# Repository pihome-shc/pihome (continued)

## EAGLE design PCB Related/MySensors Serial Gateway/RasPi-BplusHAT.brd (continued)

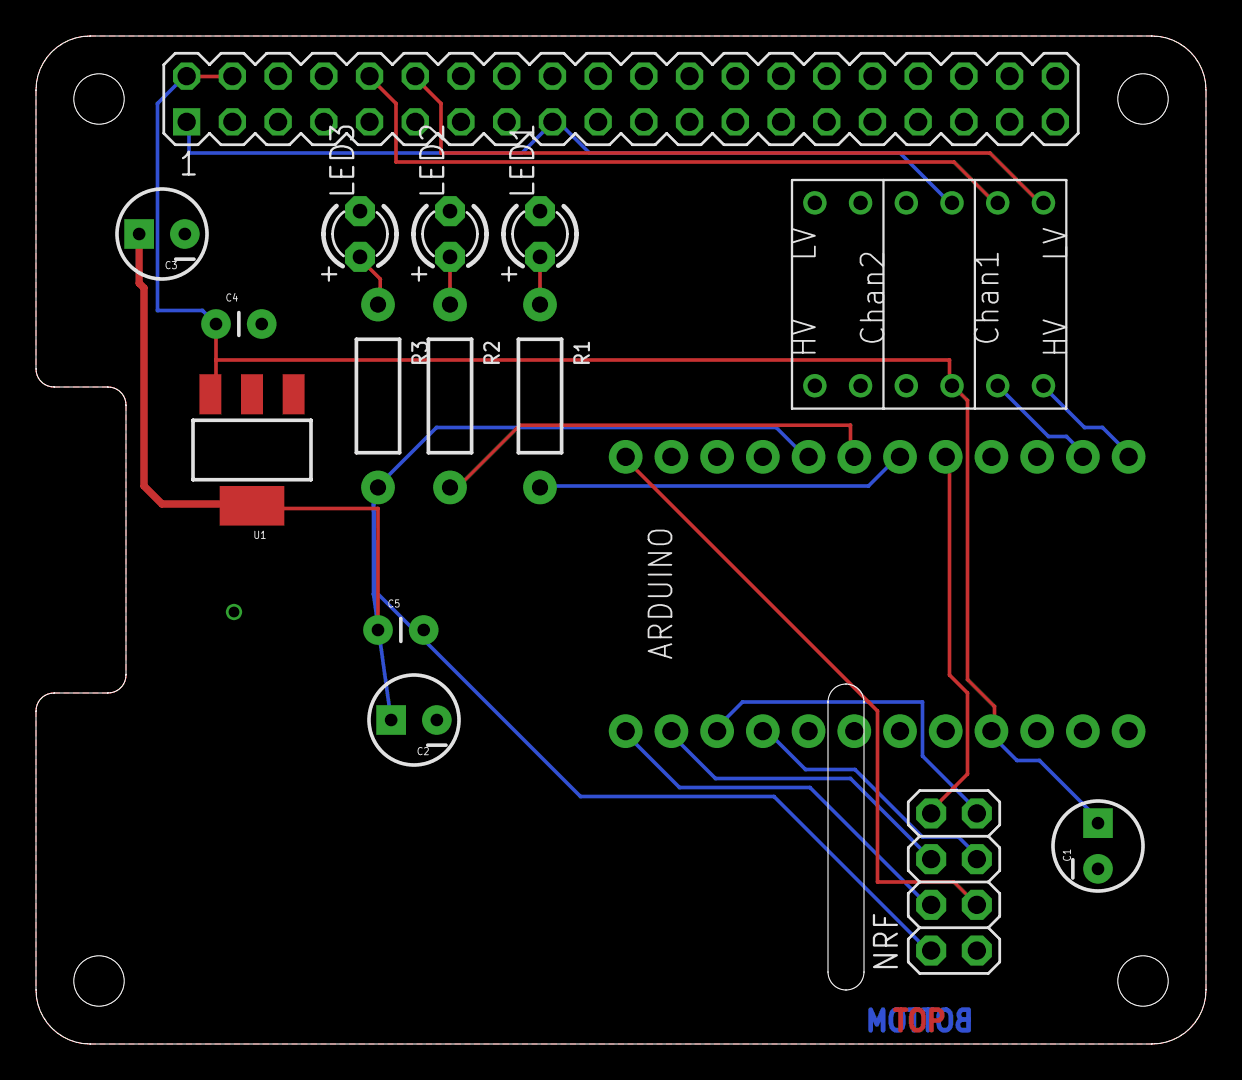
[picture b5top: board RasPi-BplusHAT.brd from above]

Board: 2 copper layers, 65.0 x 56.0 mm, 16 parts (0 on the bottom side), 20 nets.

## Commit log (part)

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2020-06-24 Update chart_load.php
    #291 changed the query from year to week and day
2020-06-25 chart load time
    reduce loading time for charts, battery voltage graph is removed.
2020-06-25 buttons for chart
    adding bigger buttons same as settings.
2020-06-28 Typo
2020-06-29 Update gpio_ds18b20.py
    gpio connected temperature senosrs,
    Charts #291
2020-06-29 Update mqtt.py
    MQTT client update: compatible with python version 3
2020-06-30 Update gateway.py
    root@pihome:~# python /var/www/cron/gateway.py
    File "/var/www/cron/gateway.py", line 223
    if (node_id != 0 and child_sensor_id != 255 and message_type == 1 and sub_type == 24):
    ^
    TabError: inconsistent use of tabs and spaces in indentation
2020-07-02 Update zone.php
    half fix for: Zone - Add - message_out not updating/populating
2020-07-09 Update db_config.ini
    chnaged the build number.
2020-07-11 MySensors Nodes without ID
    MySensors Nodes without ID #321
2020-07-13 small changes to update setup db script
    small changes to update setup db script
2020-07-14 Update gpio_ds18b20.py
    ds18B20 Wired DS18B20 Sensors and Graphs
2020-07-15 zone_type
    sync and purge column added for zone_type
    #24
2020-07-15 zone_table
    zone_table where purge is 0
    #24
2020-07-15 zone_type for db update and db setup
    #24
2020-07-15 fix for scheduling bug #331
    Bug - Scheduling #331
2020-07-17 Update zone.php
    on changing or creating zone sync value set to 0 to sync with Piconnect
    #24
2020-07-19 Update pihome_mysql_database.sql
    #24 making zone_current_state table compatible with PiConnect
2020-07-19 Update pihome_mysql_database.sql
    #24
2020-07-19 Making code compatible with PiConnect
    Making code compatible with PiConnect
    #24
2020-07-19 Update db_config.ini
    #24
2020-07-19 Update update_db.php
    #24
2020-07-19 Update boiler.php
    #24
2020-08-03 Update boiler.php
    Small fix to call home
2020-08-05 version 1.76
    version 1.76
2020-08-05 schedule name
    Schedule name on home screen moved next to zone temperature
2020-08-08 Update db.php
    sync status set to chanve for add_on #247
2020-08-18 zone editing and battery level duplicate div removed
    Zone Editing fixed updating zone_sensors table
    batteryusage: duplicate div for battery level removed.
2020-08-25 Update en.php
    Thank to Kevin for fixing typing errors.
2020-08-28 Update en.php
    improved language, thanks for Kevin for working on this.
2020-08-28 German translation
    German translation #383
2020-08-28 German translation
    #383 German translation
2020-09-09 Update boiler.php
    #391
2020-09-18 Initialization of $zone_controllers array for every zone
    Zone controllers array was not initialized for every zone, as result if zone had more than one controller and following zones executed in boiler script had less controllers, controller from previous 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
2020-09-26 Latvian language file updated
    Latvian language update,
    Thanks to @uldjan
2020-09-26 graph axis timezone
    time axis of all the charts shows up in UTC time, after this change axis time will take from browswer time.
2020-10-12 Update header.php
    missing css file removed
2020-10-25 ESP8266 Gateway sketch update with Web interface.
    ESP8266 Gateway sketch update with Web interface.
2020-10-25 Zone Graphs Records Delete from Tables
    Zone Graphs Records Delete from Tables
2020-11-05 Bug Fix for #425
    Fix for : Clicking on temperature circle deletes the schedule #425
2020-11-17 Re-Arranging sketch folder
    Re-Arranging sketch folder, now code modified in this commit
2020-12-12 Fixed error for missing " at the end of zone_sp_deadband_error string
2020-12-12 Update notice.py script for python3 and fixed a couple of issues: - wrong type cast when NULL is returned from mysql esults[bat_node_to_index['bat_level']] - missing BATTERY_NODE_INTERVAL variable - 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
2020-12-12 Fixed compilation error because of missing . in front of php variable $n_ap_mode on line 875
2021-02-17 Update db_config.ini
    build number changed
2021-02-28 HA integration
    API modification to allow Home Assistant to pull also the sensor's battery info and the boiler status.
2021-02-28 Create getZoneStatus.php
    API that allows to check the status of a zone, and the zone info (i.e. temp, battery level etc.). This approach will work both to PiHome and for MaxAir.
2021-03-08 PiHome AP Mode fix
    command for Setting up AP location is wrong and img file have IE as country code but config have GB and this is causing issues.
2021-03-13 Update index.php
    index.php updated by @twa127
2021-03-13 hotspot changes
    country code changed to GB for hotspot config file and pihome sudor added for correct
2021-03-13 Moving Hotspot to Add_on folder
    no changes just moving this to Add-On folder.
2021-03-13 Update Checklist.md5
    md5 checksum changed for two files
2021-03-17 Update db_config.ini
    updating build version
2021-03-18 Update db_config.ini
    build change changed
2021-04-26 DS18b20 filtering
    Added filtering for DS18b20 data and the option to apply exponential moving average smoothing
2021-04-26 Data filtering and EWMA
2021-05-02 Update gateway.py
    small bug fix in gateway.py
    #444
2021-07-02 Update gateway.py
    i had to remove this as this is causing problem while pinging on WIFI gateway
2021-07-23 readme images hosted on github
    readme images hosted on github
2021-07-23 images loaded from github
    images loaded from github
2021-08-08 Added HA option
    Added an option to input the MQTT details for the Home Assistant integration
2021-08-18 HA Integration Add On
    HA Integration implemented as add on
2021-09-01 Release with HA HVAC support
    Modified the HA integration to use the HA HVAC MQTT support. This creates a climate entity in HA for each zone.
2021-09-03 Override support
    Added Override support for Home Assistant integration
2021-09-28 Update boiler.php
    Changing public ip settings to improve performance
